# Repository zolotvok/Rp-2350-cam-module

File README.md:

# Rp-2350-cam-module

A compact camera board for a satellite project, built around an **RP2350B** microcontroller and an **OV5640** 5-megapixel image sensor. Two external PSRAM chips (4 MiB in total) hold full-resolution frames until they are sent out over USB, and a CAN bus interface connects the board to the rest of the satellite.

<table>
  <tr>
    <td align="center"><br>proto2, top</td>
    <td align="center"><br>proto2, bottom</td>
  </tr>
</table>

proto2 as of October 2026: parts placed, not routed yet. proto1, the manufactured board, is pictured in [its README](hardware/proto1).

## Prototypes

| Prototype | Directory | Status | Summary |
|---|---|---|---|
| **proto1** | [`hardware/proto1`](hardware/proto1) | Manufactured, brought up | First board: RP2350B, flash, 2 × PSRAM, camera on a 2×9 header. Takes photos up to 2592 × 1944 (JPEG) and streams video over USB. |
| **proto2** | [`hardware/proto2`](hardware/proto2) | In design: schematic done, PCB placed but not routed | Moves the camera's supply and clock circuitry onto the board, wires the camera directly to the RP2350B and adds a CAN bus interface, on a 40 × 40 mm board. |

Each prototype directory has its own README with the details.

## proto2 at a glance

- **MCU:** RP2350B (QFN-80), 12 MHz crystal
- **Memory:** 16 MiB QSPI flash (W25Q128JVS) and 2 × 2 MiB PSRAM (APS1604M-3SQR-SN) on the same QSPI bus; one chip-select signal is steered to either PSRAM by a 74LVC1G19, so the two chips work as two switchable banks
- **Camera:** OV5640 module on a 24-pin FPC connector, with its 2.8 V and 1.5 V regulators on the board; 8-bit parallel (DVP) interface captured with a PIO state machine and DMA; XCLK from the RP2350 (an on-board 24 MHz oscillator can be fitted instead)
- **CAN bus:** MCP2515 controller on SPI0 and SN65HVD230 transceiver, JST SH connector, jumper-selectable 120 Ω termination
- **Interfaces:** USB-C (power and data), CAN, UART with flow control, SWD
- **Board:** 4 layers, 40 × 40 mm, parts on both sides

```mermaid
flowchart LR
    USB["USB-C<br/>5 V + data"] --> MCU
    USB --> LDO["NCP1117<br/>3.3 V"]
    LDO -.->|"3.3 V"| CAMLDO["TLV74328 / TLV74315<br/>2.8 V, 1.5 V"]
    LDO -.->|"3.3 V I/O"| CAM
    CAMLDO -.-> CAM
    CAM["OV5640 module<br/>24-pin FPC"] -- "8-bit parallel (DVP)" --> MCU
    MCU["RP2350B"] -- "XCLK, I²C, reset, PWDN" --> CAM
    MCU -- "QSPI" --> FLASH["Flash<br/>16 MiB"]
    MCU -- "QSPI" --> P0["PSRAM 0<br/>2 MiB"] & P1["PSRAM 1<br/>2 MiB"]
    MCU -- "CS1 + GPIO26" --> MUX["CS demux<br/>74LVC1G19"]
    MUX -- "CE" --> P0 & P1
    MCU -- "SPI0 + INT" --> CANC["MCP2515<br/>CAN controller"]
    CANC -- "TX / RX" --> XCVR["SN65HVD230<br/>transceiver"]
    XCVR -- "CANH / CANL" --> CANBUS["CAN bus<br/>JST SH"]
```

proto1 is the same design without the CAN bus, with the camera module on a 2×9 header and on a 41.6 × 78 mm board; see [its README](hardware/proto1).

## Repository layout

```
.
├── README.md
├── LICENSE                   CC BY-SA 4.0
├── NOTICE.md                 attribution of the Adafruit designs this is based on
├── hardware/
│   ├── proto1/               first prototype, sent to manufacturing
│   │   ├── README.md
│   │   ├── kicad/            KiCad project (schematic + PCB)
│   │   ├── fabrication/      gerbers, drill files, BOM, pick-and-place
│   │   └── docs/             schematic PDF, board renders
│   └── proto2/               second prototype, work in progress
│       ├── README.md
│       ├── kicad/
│       └── docs/             schematic PDF, board renders
└── scripts/
    └── export-docs.sh        regenerates a prototype's docs/ with kicad-cli
```

## Opening the designs

The designs are KiCad 10 projects. Open `hardware/<proto>/kicad/Adafruit Metro RP2350.kicad_pro`. The project is still called *Adafruit Metro RP2350* because it started from that board's design files.

If you only want to look, the schematic of proto1 is available as a PDF in [`hardware/proto1/docs`](hardware/proto1/docs/schematic.pdf).

To regenerate the schematic PDF and the renders after changing a design (needs `kicad-cli`):

```sh
scripts/export-docs.sh proto1
```

## Firmware

The firmware and the host tools are not part of this repository. The first prototype is driven by a Pico SDK program that captures the sensor's parallel output with PIO and DMA, buffers frames in the PSRAM and sends them to a Python tool over USB.

## Acknowledgements

The designs started from two open-source hardware projects by Adafruit Industries (designed by Limor Fried/Ladyada), both licensed under CC BY-SA 3.0:

- [Adafruit Metro RP2350](https://github.com/adafruit/Adafruit-Metro-RP2350-PCB): RP2350B symbols and footprints and the base schematic
- [Adafruit OV5640 Camera Breakout](https://github.com/adafruit/Adafruit-OV5640-Camera-Breakout-PCB): the camera header pinout, and the camera supply and clock circuit used in proto2 (schematic only, the layout is not copied)

[NOTICE.md](NOTICE.md) lists what was taken from each and what was changed, and reproduces Adafruit's original notices. This project is not affiliated with or endorsed by Adafruit.

## License

The contents of this repository are licensed under the [Creative Commons Attribution-ShareAlike 4.0 International](LICENSE) license (CC BY-SA 4.0). You may use, modify and manufacture the designs, also commercially, if you give credit and share your changes under the same license.

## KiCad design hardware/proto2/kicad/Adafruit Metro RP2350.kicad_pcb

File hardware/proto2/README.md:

# proto2

Second prototype of the camera module, work in progress. It is built on [proto1](../proto1): the camera's supply and clock circuitry moves onto the board, the camera is wired straight to the RP2350B, a CAN bus interface is added, and the board shrinks to 40 × 40 mm.

<table>
  <tr>
    <td align="center"><br>top</td>
    <td align="center"><br>bottom</td>
  </tr>
</table>

Renders of the current, unrouted placement.

## Changes from proto1

- **Camera supply and clock on the board.** The support circuitry of the [Adafruit OV5640 breakout](https://github.com/adafruit/Adafruit-OV5640-Camera-Breakout-PCB) is on the board: a 24-pin OV5640 module connector (X1), 2.8 V and 1.5 V regulators (U8 TLV74328, U9 TLV74315) and a footprint for a 24 MHz oscillator (OSC1). Only the circuit comes from the breakout's schematic; the layout is not copied (see [NOTICE.md](../../NOTICE.md)).
- **Camera wired directly to the RP2350B.** The header pair between the board and the breakout (J2 on proto1, JP1/JP2 on the breakout) is gone. The camera uses the same GPIOs as on proto1, with two differences:
  - D2–D9 are on GPIO0–GPIO7 in order. The pairwise swap of proto1 is fixed, so **the firmware must not reorder the bits on proto2**.
  - The camera reset has its own net (CAM_~{RESET}, GPIO22). In the imported breakout circuit it shared the `~{RESET}` net name with the RP2350 RUN pin, which tied the camera reset to the MCU reset.
- **CAN bus.** An MCP2515 controller (U3) on SPI0 and an SN65HVD230 transceiver (U6), with a JST SH connector (J4) and a jumper-selectable 120 Ω terminator.
- **Smaller parts.** Passives are 0402 (10 µF capacitors 0603), diodes SOD-523, LEDs 0402. LCSC part numbers are filled in for JLC assembly, using basic or preferred parts where one exists.
- **Standard footprints.** Every footprint comes from the KiCad 10 standard libraries; the project needs no extra footprint library.
- **Board size.** 40 × 40 mm, 4 layers, parts on both sides (proto1: 41.6 × 78 mm).

## Status

Snapshot from October 2026:

- **Schematic:** complete apart from review. ERC still reports errors carried over from proto1 and from the imported Adafruit symbols (missing symbol libraries, undriven power pins); none of them are known to be real faults, but they have not all been checked.
- **PCB:** 40 × 40 mm outline with every part placed roughly; nothing is routed yet. In1 is a GND plane and In2 a 3.3 V plane (zones drawn, not filled).
- **To check before routing:** the orientation of the edge connectors (X1 camera FPC on the left edge, J1 USB-C on the top edge, J4 CAN in the bottom-right corner) in the 3D viewer. They were placed from the pad layout, without 3D models.

## RP2350B pin assignment

| GPIO | Signal | Connected to |
|---|---|---|
| 0–7 | DATA2–DATA9 | Camera data, D2 (LSB) to D9 (MSB) |
| 8 | EXT_XCLK | Camera clock through SJ1 |
| 9 | HSYNC | Camera HREF |
| 10 | VSYNC | Camera VSYNC |
| 11 | PCLK | Camera pixel clock |
| 16–19 | TX, RX, CTS, RTS | UART header J3 |
| 20 | SDA | Camera I²C, 10 kΩ pull-up (R12) |
| 21 | SCL | Camera I²C, 10 kΩ pull-up (R13) |
| 22 | CAM_~{RESET} | Camera reset, 10 kΩ pull-up (R10) |
| 23 | PWDN | Camera power-down, 10 kΩ pull-down (R11); LED L0 |
| 24 | USBBOOT | BOOT button S1, test point TP1 |
| 26 | GPIO26 | PSRAM bank select (74LVC1G19, U4) |
| 32 | CAN_MISO | MCP2515 SO (SPI0 RX) |
| 33 | CAN_CS | MCP2515 CS (SPI0 CSn) |
| 34 | CAN_SCK | MCP2515 SCK (SPI0 SCK) |
| 35 | CAN_MOSI | MCP2515 SI (SPI0 TX) |
| 36 | CAN_INT | MCP2515 INT (active low, push-pull) |
| 37 | CAN_STBY | SN65HVD230 Rs: low = normal (high-speed), high = standby; 10 kΩ pull-down (R32) |
| 41 | A0 | LEDs L6 and L2 |
| 42–44 | A1–A3 | LEDs L3, L4, L5 |
| 47 | PSRAM_CS | QSPI CS1, routed to one PSRAM by U4 |

The camera's I/O supply (DOVDD) is 3.3 V, the same as the RP2350's, so the camera signals need no level shifting.

## Camera clock (SJ1)

SJ1 selects where the camera's XCLK comes from. It is bridged 1–2 on the PCB, so by default the RP2350 generates XCLK on GPIO8, as on proto1, and OSC1 is not populated. GPIO8 is not a clock-output (GPOUT) pin, so XCLK has to come from PWM or PIO; it is clean only when the system clock is an integer multiple of it (150 MHz / 6 = 25 MHz, or 144 MHz / 6 = 24 MHz).

To use the on-board oscillator instead: fit OSC1 (24 MHz, 3.3 V, LCSC C712738), cut the 1–2 bridge of SJ1 and close 2–3. OSC1's enable pin is tied to 3.3 V, so it runs whenever it is fitted.

## CAN bus

- **Controller:** MCP2515 on SPI0 (max. 10 MHz SPI clock), 16 MHz crystal (Y2). Its reset comes from an RC circuit (R17, C28, D1); the RP2350 can also reset it with the SPI RESET command.
- **Transceiver:** SN65HVD230, 3.3 V. CAN_STBY (GPIO37) switches it between normal mode and standby; R32 keeps it in normal mode while GPIO37 is not driven.
- **Connector J4:** JST SH, 1.0 mm pitch, 3 pins.

  | Pin | Signal |
  |---|---|
  | 1 | CANH |
  | 2 | CANL |
  | 3 | GND |

- **Termination:** close JP3 to put 120 Ω (R31) between CANH and CANL. Close it only if this board is at one end of the bus.

## Other connectors

- **J1:** USB-C, power and data.
- **J3:** UART (1×5, 2.54 mm, not populated). Pin 1 TX, 2 RX, 3 CTS, 4 RTS, 5 GND; TX and RX are named from the RP2350's point of view.
- **DEBUG0:** SWD (1×3, 2.54 mm, not populated). Pin 1 SWCLK, 2 GND, 3 SWDIO.

## Solder jumpers

| Jumper | Default | Function |
|---|---|---|
| SJ1 | 1–2 bridged | Camera clock source, see [Camera clock](#camera-clock-sj1) |
| SJ2 | open | Connects 3.3 V to the camera's DATA1 pin, which powers the focus motor of autofocus modules. Close it only with an autofocus module: on other modules DATA1 is a data output. |
| JP3 | open | CAN bus termination |

## LEDs

| LED | Colour | Driven by | Populated |
|---|---|---|---|
| ON0 | green | 3.3 V (power indicator) | yes |
| L6 | red | GPIO41 (A0) | yes |
| L0 | red | GPIO23 (PWDN) | no |
| L2 | red | GPIO41 (A0) | no |
| L3 | green | GPIO42 (A1) | no |
| L4 | yellow | GPIO43 (A2) | no |
| L5 | blue | GPIO44 (A3) | no |

## Files

| Path | Contents |
|---|---|
| [`kicad/`](kicad) | KiCad 10 project: schematic and PCB |
| [`docs/`](docs) | [Schematic PDF](docs/schematic.pdf) and renders of the board, regenerated with `scripts/export-docs.sh proto2` |

Fabrication files will be added when the design is ready for manufacturing.

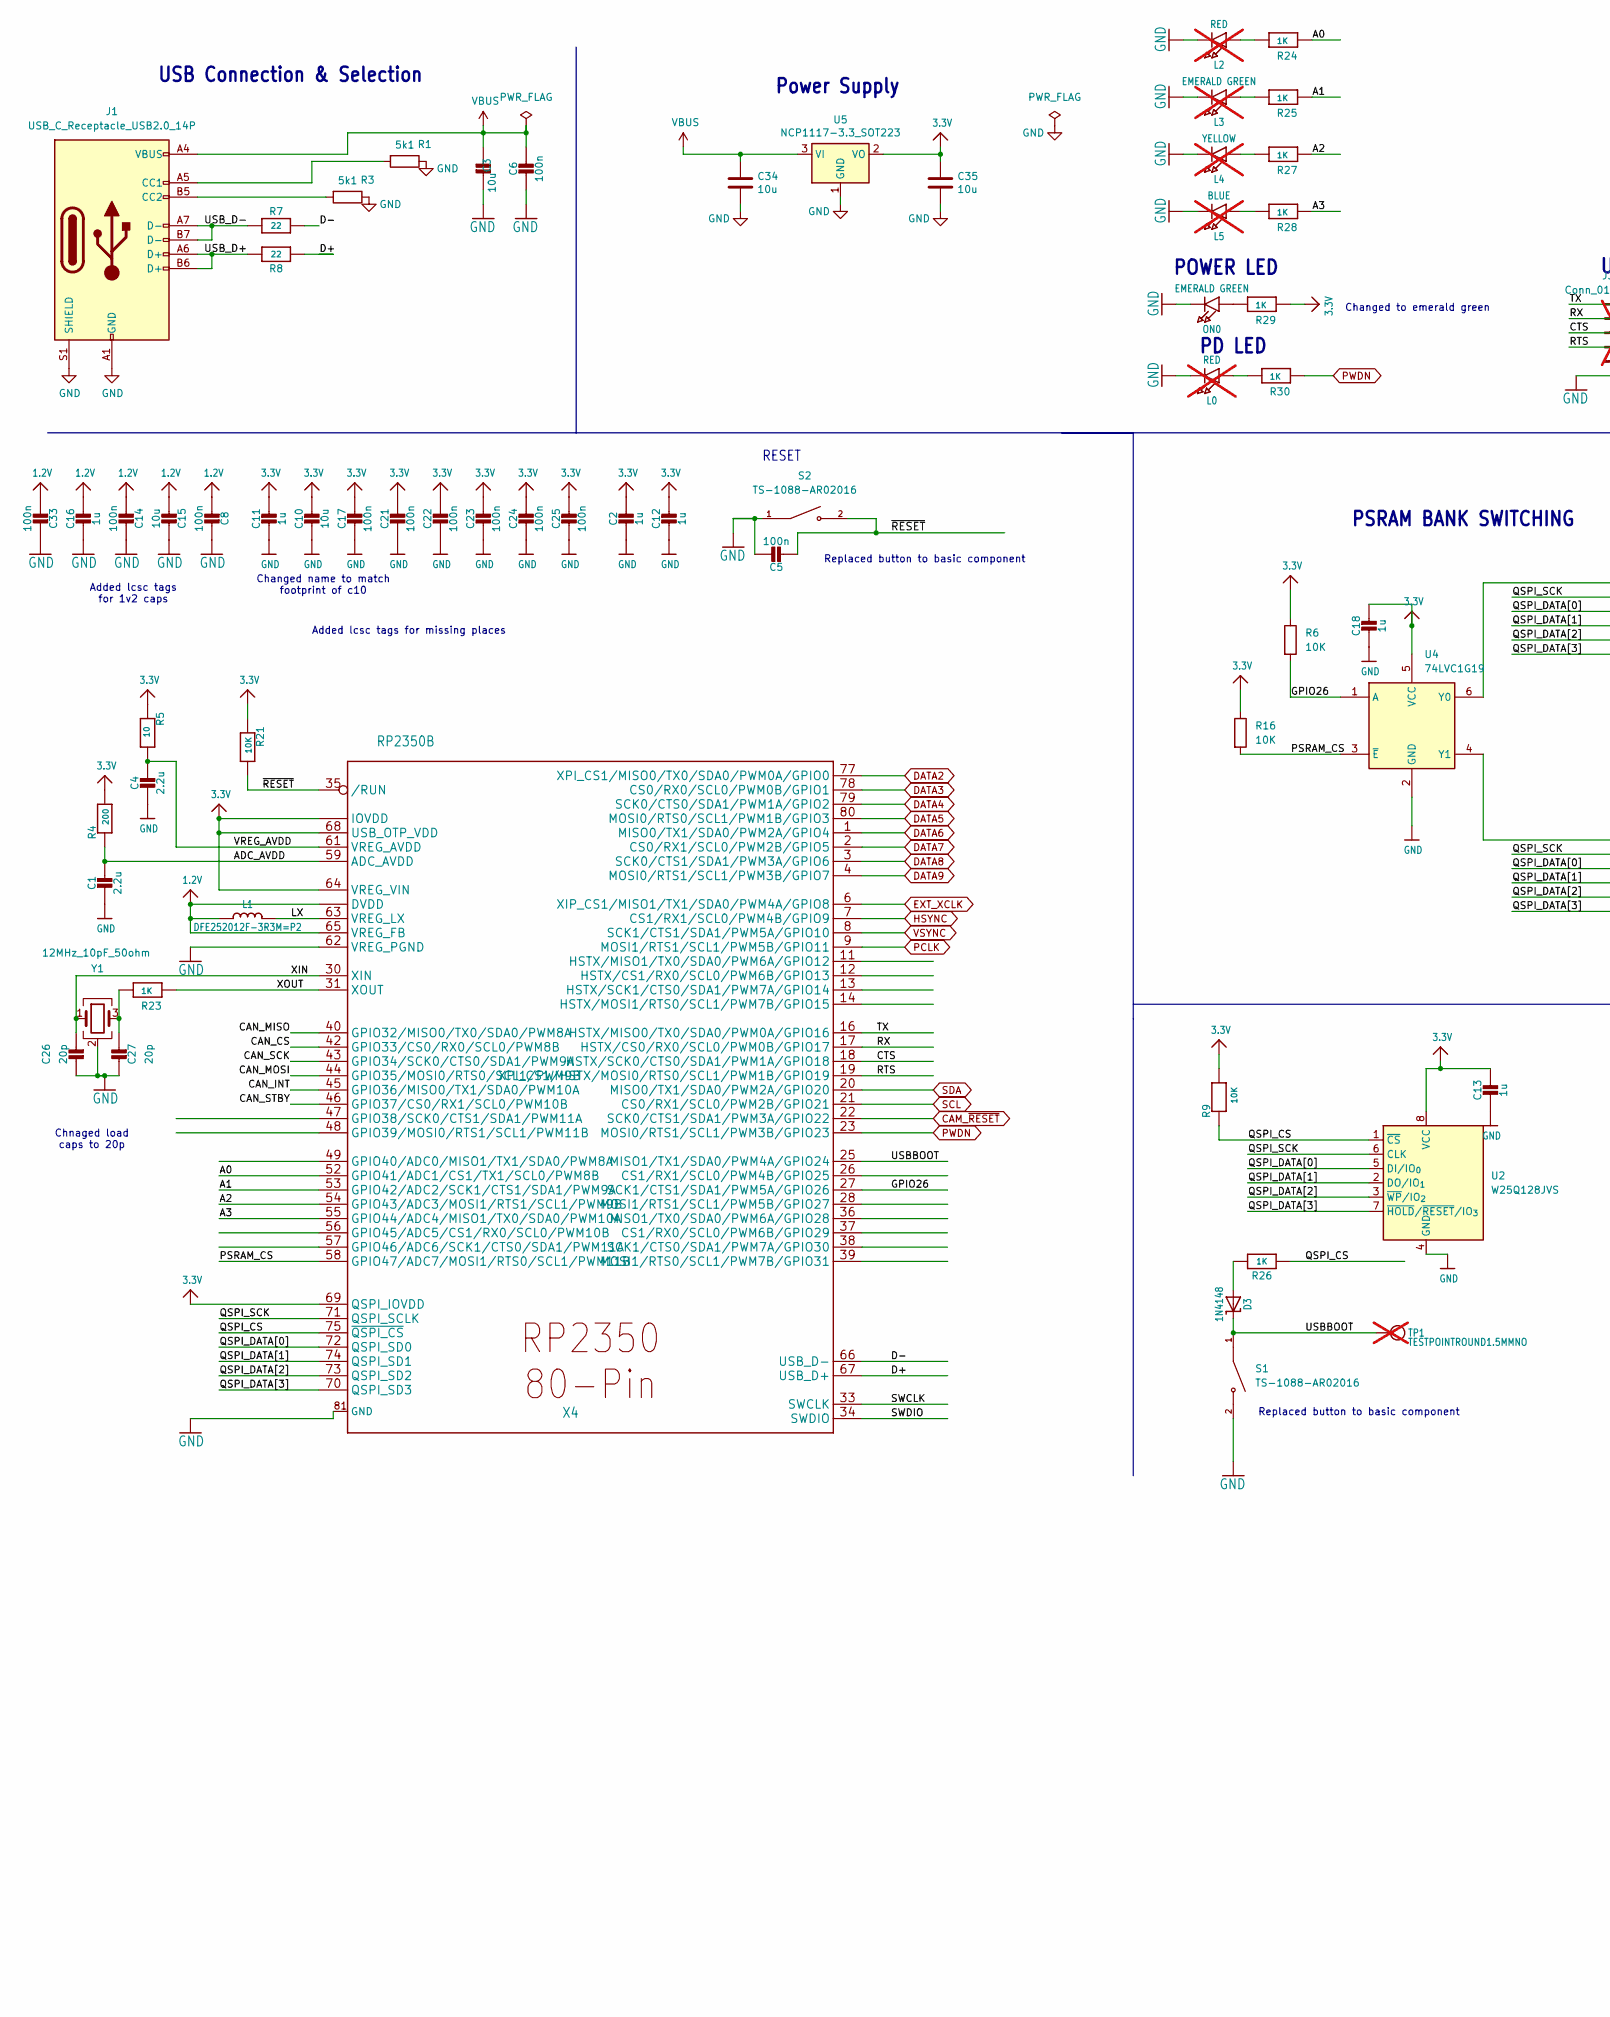
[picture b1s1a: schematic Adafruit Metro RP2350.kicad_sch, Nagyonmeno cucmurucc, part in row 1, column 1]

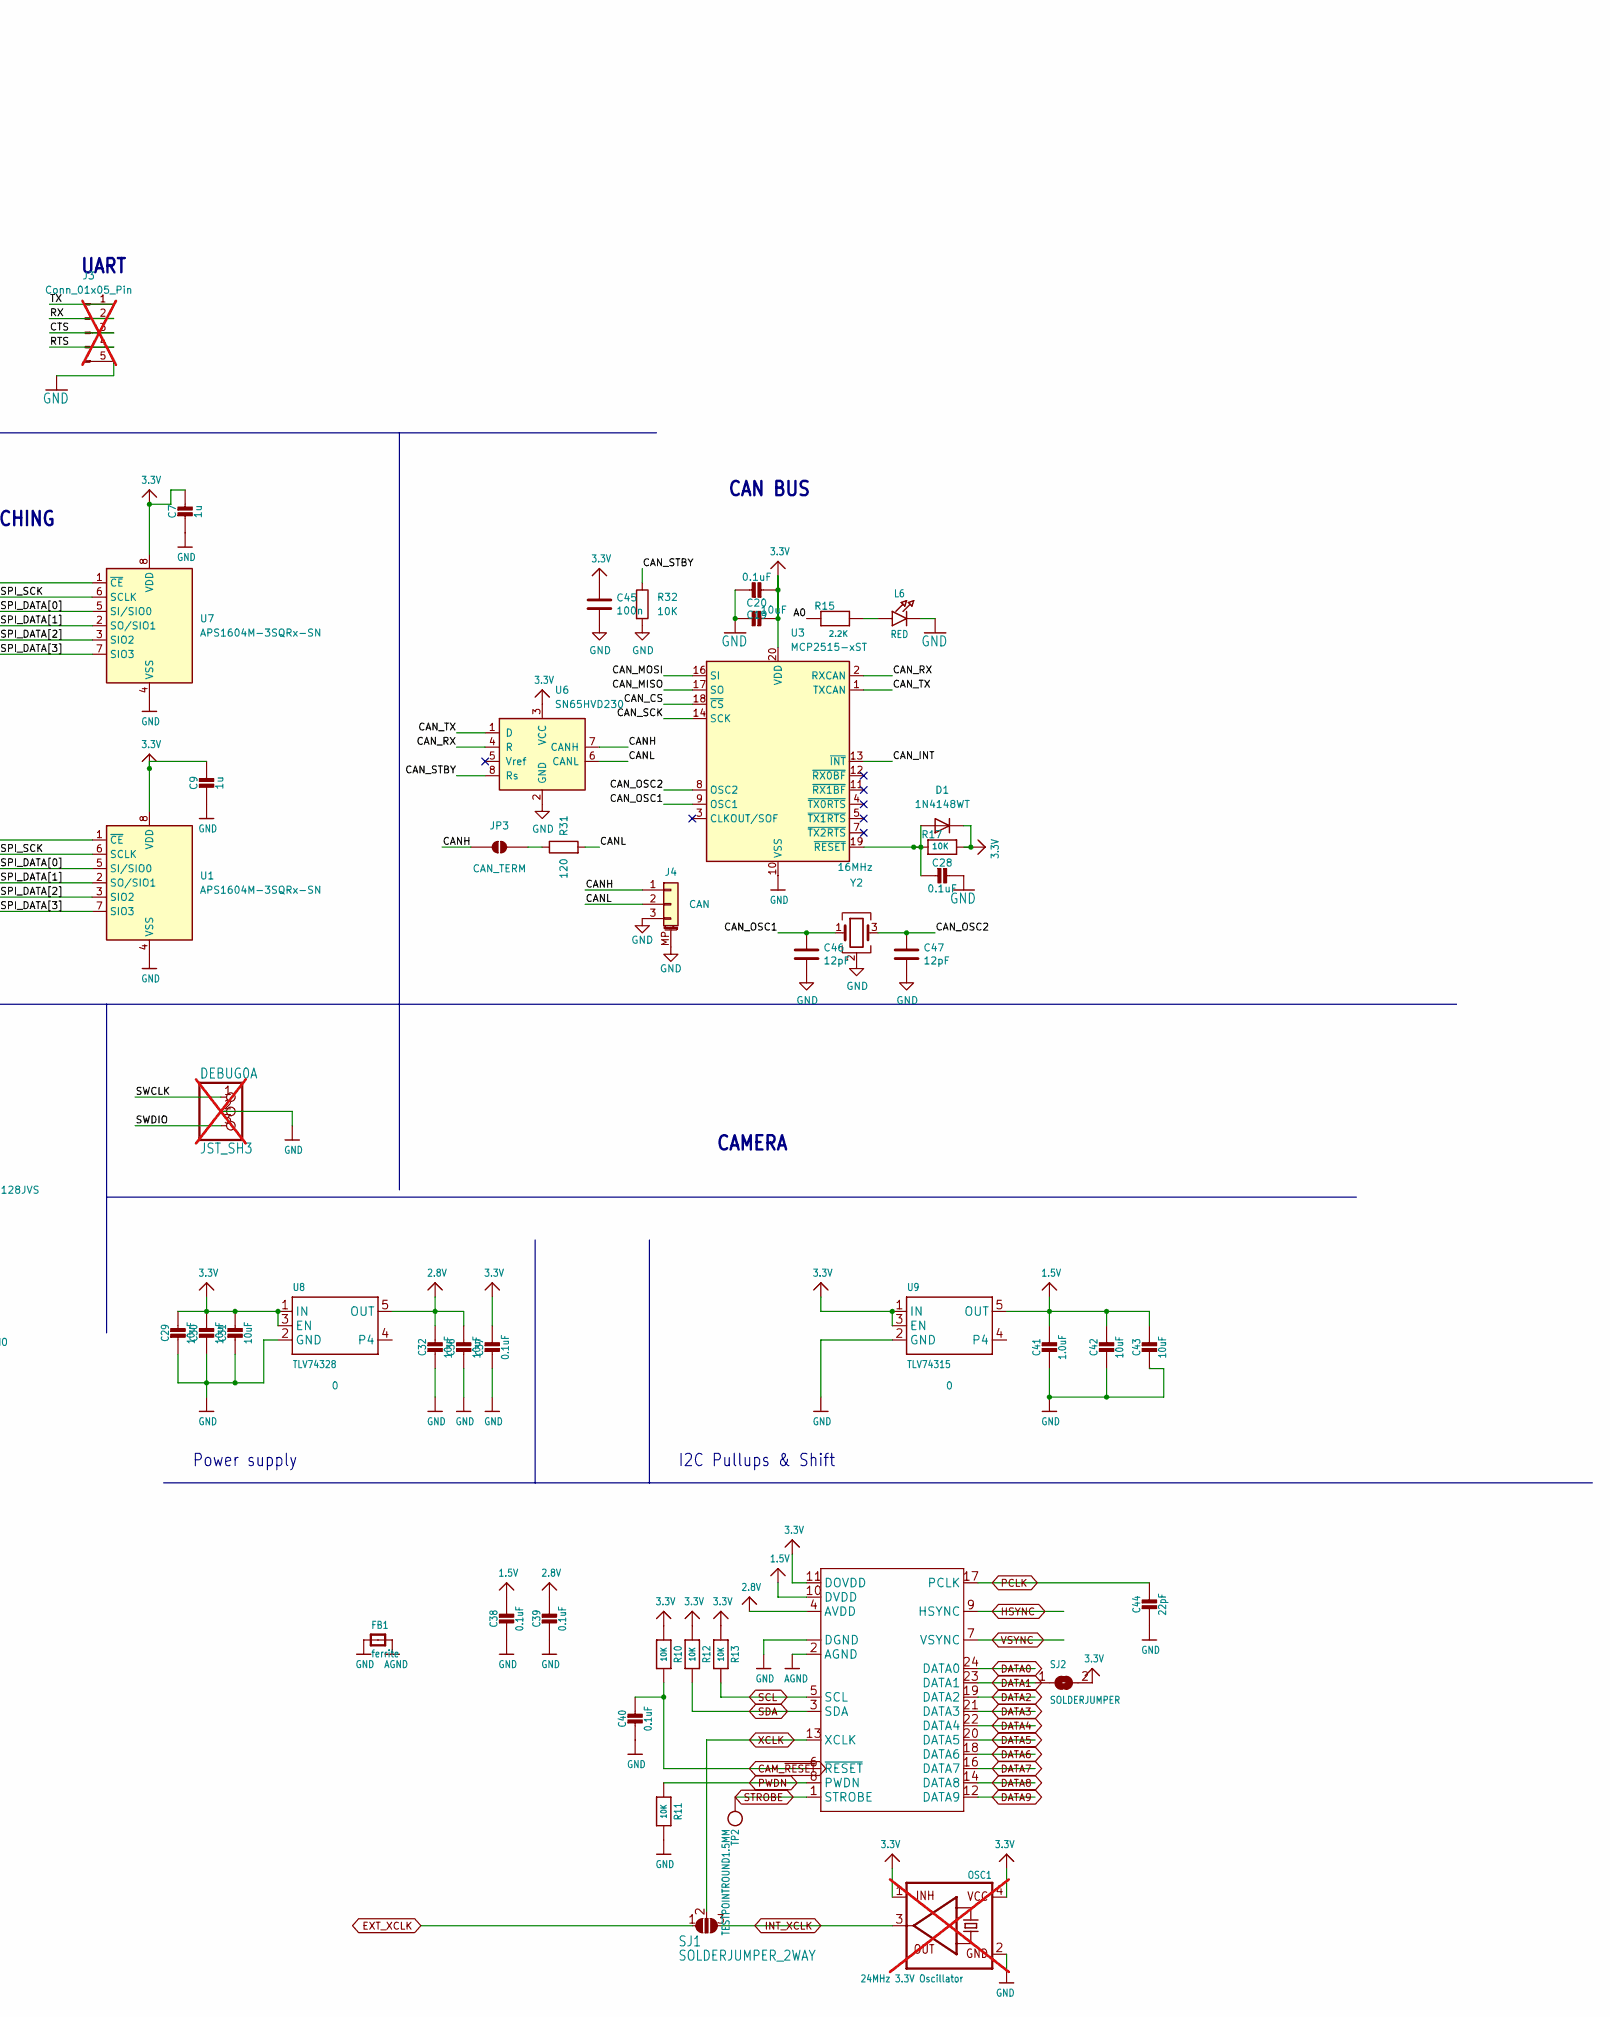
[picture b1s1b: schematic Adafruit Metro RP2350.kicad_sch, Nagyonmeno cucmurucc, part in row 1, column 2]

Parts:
C1, C4: 2.2u; C_0402_1005Metric; LCSC C12530
C2, C7, C9, C11, C12, C13, C16, C18: 1u; C_0402_1005Metric; LCSC C52923
C3, C10, C15, C34, C35: 10u; C_0603_1608Metric; LCSC C96446
C5, C6, C8, C14, C17, C21, C22, C23, C24, C25, C33, C45: 100n; C_0402_1005Metric; LCSC C1525
C19, C29, C30, C31, C32, C36, C42, C43: 10uF; C_0603_1608Metric; LCSC C96446
C20, C28, C37, C38, C39, C40: 0.1uF; C_0402_1005Metric; LCSC C1525
C26, C27: 20p; C_0402_1005Metric; LCSC C1554
C41: 1.0uF; C_0402_1005Metric; LCSC C52923
C44: 22pF; C_0402_1005Metric; LCSC C1555
C46, C47: 12pF; C_0402_1005Metric; LCSC C1547
D1: 1N4148WT; D_SOD-523; LCSC C7420320
D3: 1N4148; D_SOD-523; LCSC C7420320
DEBUG0: JST_SH3; PinHeader_1x03_P2.54mm_Vertical; not fitted
FB1: ferrite; L_0402_1005Metric; LCSC C76886
J1: USB_C_Receptacle_USB2.0_14P; USB_C_Receptacle_XKB_U262-16XN-4BVC11; LCSC C2765186
J3: Conn_01x05_Pin; PinHeader_1x05_P2.54mm_Vertical; LCSC C22438173; not fitted
J4: CAN; JST_SH_SM03B-SRSS-TB_1x03-1MP_P1.00mm_Horizontal; LCSC C7430445
JP3: CAN_TERM; SolderJumper-2_P1.3mm_Open_RoundedPad1.0x1.5mm
L0, L2: RED; LED_0402_1005Metric; LCSC C25503345; not fitted
L1: DFE252012F-3R3M=P2; L_1210_3225Metric; LCSC C2046640
L3: EMERALD GREEN; LED_0402_1005Metric; LCSC C965793; not fitted
L4: YELLOW; LED_0402_1005Metric; LCSC C25503856; not fitted
L5: BLUE; LED_0402_1005Metric; LCSC C22355736; not fitted
L6: RED; LED_0402_1005Metric; LCSC C25503345
ON0: EMERALD GREEN; LED_0402_1005Metric; LCSC C965793
OSC1: 24MHz 3.3V Oscillator; Oscillator_SMD_Abracon_ASE-4Pin_3.2x2.5mm; LCSC C712738; not fitted
R1, R3: 5k1; R_0402_1005Metric; LCSC C25905
R4: 200; R_0402_1005Metric; LCSC C25087
R5: 10; R_0402_1005Metric; LCSC C25077
R6, R9, R10, R11, R12, R13, R16, R17, R21, R32: 10K; R_0402_1005Metric; LCSC C25744
R7, R8: 22; R_0402_1005Metric; LCSC C25092
R15: 2.2K; R_0402_1005Metric; LCSC C25879
R23, R24, R25, R26, R27, R28, R29, R30: 1K; R_0402_1005Metric; LCSC C11702
R31: 120; R_0402_1005Metric; LCSC C25079
S1, S2: TS-1088-AR02016; SW_SPST_TS-1088-xR020; PARTREV N/A; LCSC C720477
SJ1: SOLDERJUMPER_2WAY; SolderJumper-3_P1.3mm_Bridged12_RoundedPad1.0x1.5mm_NumberL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
SJ2: SOLDERJUMPER; SolderJumper-2_P1.3mm_Open_RoundedPad1.0x1.5mm
TP1: TESTPOINTROUND1.5MMNO; TestPoint_Pad_D1.0mm; not fitted
TP2: TESTPOINTROUND1.5MM; TestPoint_Pad_D1.5mm
U1, U7: APS1604M-3SQRx-SN; SOIC-8_3.9x4.9mm_P1.27mm; LCSC C18214056
U2: W25Q128JVS; SOIC-8_5.3x5.3mm_P1.27mm; LCSC C97521
U3: MCP2515-xST; TSSOP-20_4.4x6.5mm_P0.65mm; LCSC C609745
U4: 74LVC1G19; SOT-363_SC-70-6; LCSC C148208
U5: NCP1117-3.3_SOT223; SOT-223-3_TabPin2; LCSC C6186
U6: SN65HVD230; SOIC-8_3.9x4.9mm_P1.27mm; LCSC C16468
U8: TLV74328; SOT-23-5; JLC_ROTATION 270
U9: TLV74315; SOT-23-5; JLC_ROTATION 270
X1: CAMERA_OV2640; Jushuo_AFC07-S24FCA-00_1x24-1MP_P0.50_Horizontal; LCSC C262567
X4: RP2350B; QFN-80-1EP_10x10mm_P0.4mm_EP3.4x3.4mm; LCSC C42415655
Y1: 12MHz_10pF_50ohm; Crystal_SMD_3225-4Pin_3.2x2.5mm; LCSC C9002
Y2: 16MHz; Crystal_SMD_3225-4Pin_3.2x2.5mm; LCSC C13738

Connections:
1.2V: C8.2, C14.2, C15.2, C16.1, C33.2, L1.1, X4.10 (DVDD), X4.32 (DVDD), X4.51 (DVDD), X4.65 (VREG_FB)
1.5V: C38.1, C41.1, C42.1, C43.1, U9.5 (OUT), X1.10 (DVDD)
2.8V: C32.1, C36.1, C39.1, U8.5 (OUT), X1.4 (AVDD)
3.3V: C2.1, C7.1, C9.1, C10.1, C11.1, C12.1, C13.1, C17.1, C18.1, C19.1, C20.2, C21.1, C22.1, C23.1, C24.1, C25.1, C29.1, C30.1, C31.1, C35.1, C37.1, C45.1, D1.1 (K), OSC1.1 (INH), OSC1.4 (VCC), R4.2, R5.1, R6.1, R9.2, R10.1, R12.1, R13.1, R16.1, R17.2, R21.1, R29.2, SJ2.2, U1.8 (VDD), U2.8 (VCC), U3.20 (VDD), U4.5 (VCC), U5.2 (VO), U6.3 (VCC), U7.8 (VDD), U8.1 (IN), U8.3 (EN), U9.1 (IN), U9.3 (EN), X1.11 (DOVDD), X4.5 (IOVDD), X4.15 (IOVDD), X4.24 (IOVDD), X4.29 (IOVDD), X4.41 (IOVDD), X4.50 (IOVDD), X4.60 (IOVDD), X4.64 (VREG_VIN), X4.68 (USB_OTP_VDD), X4.69 (QSPI_IOVDD), X4.76 (IOVDD)
/A0: R15.1, R24.2, X4.52 (GPIO41/ADC1/CS1/TX1/SCL0/PWM8B)
/A1: R25.2, X4.53 (GPIO42/ADC2/SCK1/CTS1/SDA1/PWM9A)
/A2: R27.2, X4.54 (GPIO43/ADC3/MOSI1/RTS1/SCL1/PWM9B)
/A3: R28.2, X4.55 (GPIO44/ADC4/MISO1/TX0/SDA0/PWM10A)
/ADC_AVDD: C1.1, R4.1, X4.59 (ADC_AVDD)
/CANH: J4.1, JP3.1 (A), U6.7 (CANH)
/CANL: J4.2, R31.2, U6.6 (CANL)
/CAN_CS: U3.18 (~CS), X4.42 (GPIO33/CS0/RX0/SCL0/PWM8B)
/CAN_INT: U3.13 (~INT), X4.45 (GPIO36/MISO0/TX1/SDA0/PWM10A)
/CAN_MISO: U3.17 (SO), X4.40 (GPIO32/MISO0/TX0/SDA0/PWM8A)
/CAN_MOSI: U3.16 (SI), X4.44 (GPIO35/MOSI0/RTS0/SCL1/PWM9B)
/CAN_OSC1: C46.1, U3.9 (OSC1), Y2.1
/CAN_OSC2: C47.1, U3.8 (OSC2), Y2.3
/CAN_RX: U3.2 (RXCAN), U6.4 (R)
/CAN_SCK: U3.14 (SCK), X4.43 (GPIO34/SCK0/CTS0/SDA1/PWM9A)
/CAN_STBY: R32.1, U6.8 (Rs), X4.46 (GPIO37/CS0/RX1/SCL0/PWM10B)
/CAN_TX: U3.1 (TXCAN), U6.1 (D)
/CTS: J3.3, X4.18 (HSTX/SCK0/CTS0/SDA1/PWM1A/GPIO18)
/D+: R8.2, X4.67 (USB_D+)
/D-: R7.2, X4.66 (USB_D-)
/GPIO26: R6.2, U4.1 (A), X4.27 (SCK1/CTS1/SDA1/PWM5A/GPIO26)
/LX: L1.2, X4.63 (VREG_LX)
/PSRAM_CS: R16.2, U4.3 (~E), X4.58 (GPIO47/ADC7/MOSI1/RTS0/SCL1/PWM11B)
/QSPI_CS: R9.1, R26.1, U2.1 (~CS), X4.75 (~QSPI_CS)
/QSPI_DATA[0]: U1.5 (SI/SIO0), U2.5 (DI/IO_{0}), U7.5 (SI/SIO0), X4.72 (QSPI_SD0)
/QSPI_DATA[1]: U1.2 (SO/SIO1), U2.2 (DO/IO_{1}), U7.2 (SO/SIO1), X4.74 (QSPI_SD1)
/QSPI_DATA[2]: U1.3 (SIO2), U2.3 (~WP/IO_{2}), U7.3 (SIO2), X4.73 (QSPI_SD2)
/QSPI_DATA[3]: U1.7 (SIO3), U2.7 (~HOLD/~RESET/IO_{3}), U7.7 (SIO3), X4.70 (QSPI_SD3)
/QSPI_SCK: U1.6 (SCLK), U2.6 (CLK), U7.6 (SCLK), X4.71 (QSPI_SCLK)
/RTS: J3.4, X4.19 (XPI_CS1/HSTX/MOSI0/RTS0/SCL1/PWM1B/GPIO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)
/RX: J3.2, X4.17 (HSTX/CS0/RX0/SCL0/PWM0B/GPIO17)
/SWCLK: DEBUG0.1, X4.33 (SWCLK)
/SWDIO: DEBUG0.3, X4.34 (SWDIO)
/TX: J3.1, X4.16 (HSTX/MISO0/TX0/SDA0/PWM0A/GPIO16)
/USBBOOT: D3.1 (C), S1.1, TP1.1 (P$1_1), X4.25 (MISO1/TX1/SDA0/PWM4A/GPIO24)
/USB_D+: J1.A6 (D+), J1.B6 (D+), R8.1
/USB_D-: J1.A7 (D-), J1.B7 (D-), R7.1
/VREG_AVDD: C4.1, R5.2, X4.61 (VREG_AVDD)
/XIN: C26.2, X4.30 (XIN), Y1.1
/XOUT: R23.2, X4.31 (XOUT)
/~RESET: C5.2, R21.2, S2.2, X4.35 (/RUN)
AGND: FB1.2, X1.2 (AGND)
CAM_~RESET: C40.1, R10.2, X1.6 (~RESET), X4.22 (SCK0/CTS1/SDA1/PWM3A/GPIO22)
DATA0: X1.24 (DATA0)
DATA1: SJ2.1, X1.23 (DATA1)
DATA2: X1.19 (DATA2), X4.77 (XPI_CS1/MISO0/TX0/SDA0/PWM0A/GPIO0)
DATA3: X1.21 (DATA3), X4.78 (CS0/RX0/SCL0/PWM0B/GPIO1)
DATA4: X1.22 (DATA4), X4.79 (SCK0/CTS0/SDA1/PWM1A/GPIO2)
DATA5: X1.20 (DATA5), X4.80 (MOSI0/RTS0/SCL1/PWM1B/GPIO3)
DATA6: X1.18 (DATA6), X4.1 (MISO0/TX1/SDA0/PWM2A/GPIO4)
DATA7: X1.16 (DATA7), X4.2 (CS0/RX1/SCL0/PWM2B/GPIO5)
DATA8: X1.14 (DATA8), X4.3 (SCK0/CTS1/SDA1/PWM3A/GPIO6)
DATA9: X1.12 (DATA9), X4.4 (MOSI0/RTS1/SCL1/PWM3B/GPIO7)
EXT_XCLK: SJ1.1, X4.6 (XIP_CS1/MISO1/TX1/SDA0/PWM4A/GPIO8)
GND: C1.2, C2.2, C3.1, C4.2, C5.1, C6.2, C7.2, C8.1, C9.2, C10.2, C11.2, C12.2, C13.2, C14.1, C15.1, C16.2, C17.2, C18.2, C19.2, C20.1, C21.2, C22.2, C23.2, C24.2, C25.2, C26.1, C27.1, C28.1, C29.2, C30.2, C31.2, C32.2, C33.1, C34.2, C35.2, C36.2, C37.2, C38.2, C39.2, C40.2, C41.2, C42.2, C43.2, C44.2, C45.2, C46.2, C47.2, DEBUG0.2, FB1.1, J1.A1 (GND), J1.A12 (GND), J1.B1 (GND), J1.B12 (GND), J1.S1 (SHIELD), J3.5, J4.3, J4.MP (MountPin), L0.1 (C), L2.1 (C), L3.1 (C), L4.1 (C), L5.1 (C), L6.1 (C), ON0.1 (C), OSC1.2 (GND), R1.1, R3.1, R11.2, R32.2, S1.2, S2.1, U1.4 (VSS), U2.4 (GND), U3.10 (VSS), U4.2 (GND), U5.1 (GND), U6.2 (GND), U7.4 (VSS), U8.2 (GND), U9.2 (GND), X1.15 (DGND), X1.MP (DGND), X4.62 (VREG_PGND), X4.81 (GND), Y1.2 (G), Y1.4 (G), Y2.2 (G), Y2.4 (G)
HSYNC: X1.9 (HSYNC), X4.7 (CS1/RX1/SCL0/PWM4B/GPIO9)
INT_XCLK: OSC1.3 (OUT), SJ1.3
unnamed: C27.2, R23.1, Y1.3
unnamed: C28.2, D1.2 (A), R17.1, U3.19 (~RESET)
unnamed: D3.2 (A), R26.2
unnamed: J1.A5 (CC1), R1.2
unnamed: J1.B5 (CC2), R3.2
unnamed: JP3.2 (B), R31.1
unnamed: L0.2 (A), R30.1
unnamed: L2.2 (A), R24.1
unnamed: L3.2 (A), R25.1
unnamed: L4.2 (A), R27.1
unnamed: L5.2 (A), R28.1
unnamed: L6.2 (A), R15.2
unnamed: ON0.2 (A), R29.1
unnamed: U1.1 (~CE), U4.4 (Y1)
unnamed: U4.6 (Y0), U7.1 (~CE)
PCLK: C44.1, X1.17 (PCLK), X4.9 (MOSI1/RTS1/SCL1/PWM5B/GPIO11)
PWDN: R11.1, R30.2, X1.8 (PWDN), X4.23 (MOSI0/RTS1/SCL1/PWM3B/GPIO23)
SCL: R13.2, X1.5 (SCL), X4.21 (CS0/RX1/SCL0/PWM2B/GPIO21)
SDA: R12.2, X1.3 (SDA), X4.20 (MISO0/TX1/SDA0/PWM2A/GPIO20)
STROBE: TP2.1 (P$1_1), X1.1 (STROBE)
VBUS: C3.2, C6.1, C34.1, J1.A4 (VBUS), J1.A9 (VBUS), J1.B4 (VBUS), J1.B9 (VBUS), U5.3 (VI)
VSYNC: X1.7 (VSYNC), X4.8 (SCK1/CTS1/SDA1/PWM5A/GPIO10)
XCLK: SJ1.2, X1.13 (XCLK)

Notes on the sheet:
Changed name to match footprint of c10
Changed to emerald green
PSRAM BANK SWITCHING
Added lcsc tags for missing places
CAN BUS
POWER LED
Added lcsc tags for 1v2 caps
CAMERA
Power Supply
Chnaged load caps to 20p
I2C Pullups & Shift
RESET
Replaced button to basic component
UART
USB Connection & Selection
PD LED
Power supply

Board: 4 copper layers, 109 parts (61 on the bottom side), 83 nets, no tracks yet.

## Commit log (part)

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2026-05-04 second commit
2026-06-26 prot1
